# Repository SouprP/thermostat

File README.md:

# Intelligent Thermostat

Hardware part of the thermostat project, made for Raspberry Pi Pico W to allow easier data gathering from sensors and control of temperature.

## Tools used

- Kicad
- C / C++
- CMake
- lwIP
- PicoSDK

## Schematics and PCB design

The schematic below is a simplified version of the schematic provided
inside the ```/hardware/``` folder.

<br>
<br>

<br>
<br>

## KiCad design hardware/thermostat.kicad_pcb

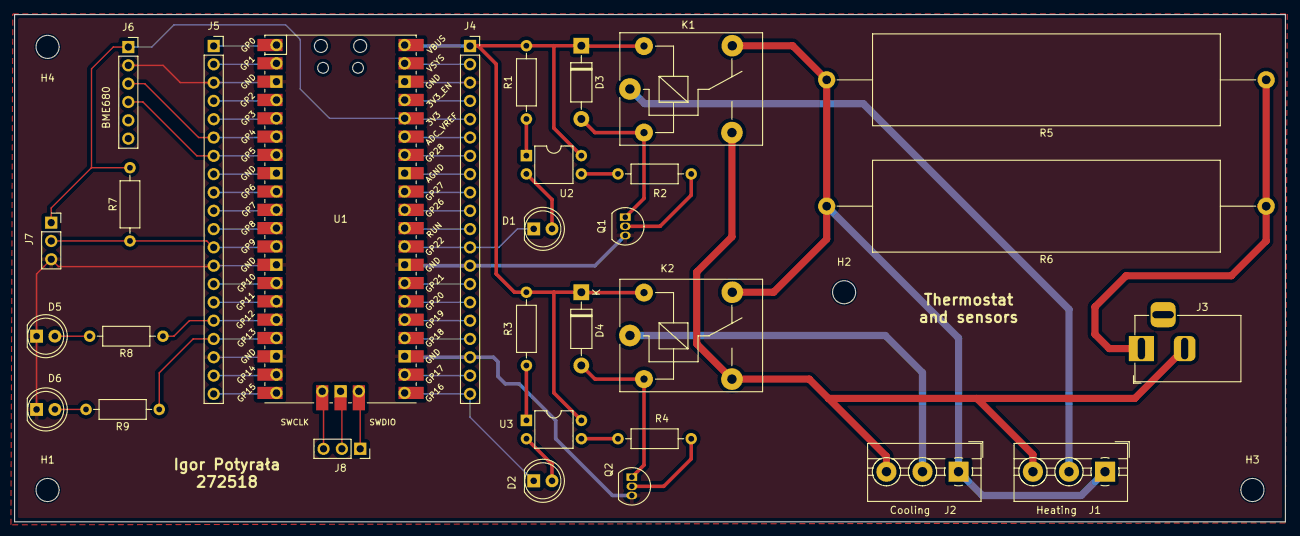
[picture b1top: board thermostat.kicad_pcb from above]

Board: 2 copper layers, 176.3 x 70.4 mm, 34 parts (0 on the bottom side), 55 nets.

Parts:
D1, D2, D5, D6: LED; LED_D5.0mm
D3, D4: 1N4007; D_DO-41_SOD81_P10.16mm_Horizontal
H1, H2, H3, H4: MountingHole; MountingHole_3.2mm_M3
J1: Heating; TerminalBlock_MaiXu_MX126-5.0-03P_1x03_P5.00mm
J2: Cooling; TerminalBlock_MaiXu_MX126-5.0-03P_1x03_P5.00mm
J3: Jack-DC; BarrelJack_Horizontal
J4, J5: Conn_01x20_Socket; PinSocket_1x20_P2.54mm_Vertical
J6: BME680; PinSocket_1x06_P2.54mm_Vertical
J7, J8: Conn_01x03_Socket; PinSocket_1x03_P2.54mm_Vertical
K1, K2: Relay; Relay_SPDT_SANYOU_SRD_Series_Form_C
Q1, Q2: BC547; TO-92_Inline
R1, R2, R3, R4, R7, R8, R9: R; R_Axial_DIN0207_L6.3mm_D2.5mm_P10.16mm_Horizontal
R5, R6: R; R_Axial_Power_L48.0mm_W12.5mm_P60.96mm
U1: Pico; RPi_Pico_SMD_TH
U2, U3: PC817; DIP-4_W7.62mm

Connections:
3V3: J4.5, J6.1, J7.1, R7.2, U1.36 (3V3)
5V: D3.1 (K), D4.1 (K), J4.1, K1.5, K2.5, R1.1, R3.1, U1.40 (VBUS), U2.4, U3.4
12V: J1.1, J2.1, K1.4, K2.4, R5.2, R6.2
COLD_GPIO: D2.1 (K), J4.20, U1.21 (GPIO16)
COM C: J2.2, K2.1
COM H: J1.2, K1.1
DS18B20: J5.12, J7.2, R7.1, U1.12 (GPIO9)
GND: D5.1 (K), D6.1 (K), J4.3, J4.13, J4.18, J5.3, J5.13, J5.18, J6.2, J7.3, Q1.3 (E), Q2.3 (E), U1.3 (GND), U1.13 (GND), U1.18 (GND), U1.23 (GND), U1.28 (GND), U1.38 (GND)
GND 12V: J1.3, J2.3, J3.2, K1.3, K2.3
HEAT_GPIO: D1.1 (K), J4.12, U1.29 (GPIO22)
LED_1: J5.16, R8.1, U1.16 (GPIO12)
LED_2: J5.17, R9.1, U1.17 (GPIO13)
unnamed: D1.2 (A), U2.2
unnamed: D2.2 (A), U3.2
unnamed: D3.2 (A), K1.2, Q1.1 (C)
unnamed: D4.2 (A), K2.2, Q2.1 (C)
unnamed: D5.2 (A), R8.2
unnamed: D6.2 (A), R9.2
unnamed: J3.1, R5.1, R6.1
unnamed: J4.2, U1.39 (VSYS)
unnamed: J4.4, U1.37 (3V3_EN)
unnamed: J4.6, U1.35 (ADC_VREF)
unnamed: J4.7, U1.34 (GPIO28_ADC2)
unnamed: J4.8, U1.33 (AGND)
unnamed: J4.9, U1.32 (GPIO27_ADC1)
unnamed: J4.10, U1.31 (GPIO26_ADC0)
unnamed: J4.11, U1.30 (RUN)
unnamed: J4.14, U1.27 (GPIO21)
unnamed: J4.15, U1.26 (GPIO20)
unnamed: J4.16, U1.25 (GPIO19)
unnamed: J4.17, U1.24 (GPIO18)
unnamed: J4.19, U1.22 (GPIO17)
unnamed: J5.1, U1.1 (GPIO0)
unnamed: J5.2, U1.2 (GPIO1)
unnamed: J5.4, U1.4 (GPIO2)
unnamed: J5.5, U1.5 (GPIO3)
unnamed: J5.8, U1.8 (GND)
unnamed: J5.9, U1.9 (GPIO6)
unnamed: J5.10, U1.10 (GPIO7)
unnamed: J5.11, U1.11 (GPIO8)
unnamed: J5.14, U1.14 (GPIO10)
unnamed: J5.15, U1.15 (GPIO11)
unnamed: J5.19, U1.19 (GPIO14)
unnamed: J5.20, U1.20 (GPIO15)
unnamed: J8.1, U1.43 (SWDIO)
unnamed: J8.2, U1.42 (GND)
unnamed: J8.3, U1.41 (SWCLK)
unnamed: Q1.2 (B), R2.2
unnamed: Q2.2 (B), R4.2
unnamed: R1.2, U2.1
unnamed: R2.1, U2.3
unnamed: R3.2, U3.1
unnamed: R4.1, U3.3
SCL: J5.7, J6.4, U1.7 (GPIO5)
SDA: J5.6, J6.3, U1.6 (GPIO4)

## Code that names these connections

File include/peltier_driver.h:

#ifndef PELTIER_DRIVER_H_
#define PELTIER_DRIVER_H_

#define PICO_MUTEX_ENABLE_SDK120_COMPATIBILITY 1

#include <pico/stdlib.h>
#include <hardware/gpio.h>
#include <pico/multicore.h>
#include <pico/mutex.h>
#include <stdio.h>
#include <stdlib.h>
#include <time.h>

#include <sensors/ds18b20.h>
#include "hardware/sync.h"
#include <pico/stdlib.h>

class PeltierDriver{
    private:
        // GPIOs for controlling the H bridge
        uint8_t HEAT_GPIO;
        uint8_t COLD_GPIO;

        // temperature sensor attachated to the peltier module
        DS18B20 *ds18b20;

        // target temperature for debugging
        float target_temp = 35.0f;
        float offset = 2.0f;

        // is heating up or cooling down
        // bool isWorking;
        bool isCooling;
        bool isHeating;

        // mutex for sync
        static mutex_t peltier_mutex;

    public:
        // PeltierDriver();
        // ~PeltierDriver();

        void init(uint8_t heat_gpio, uint8_t cold_gpio, DS18B20 *ds18b20);
        void set_target_temp(float target_temp);
        float get_target_temp();
        float get_temp();
        void drive();
};

#endif

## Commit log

2024-11-18 Setup and DS18B20
2024-11-28 Peltier driver + BME680 partialy done
2025-01-13 WiFi, BME680 and other
2025-04-01 README.md and hardware files
